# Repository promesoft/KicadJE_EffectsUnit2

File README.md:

# KicadJE_EffectsUnit2
Distortion test base

# Purpose
Use for Distortion Effects unit and Distortion pedal

# Status - Preliminary SCH/PCB Mounted
## Initial 
| Stage  | Detail | Status |
| ------------- | ------------- | ------------- |
| create material  | sch/pcb | OK  |
| | gerber | OK |
| production  |   | done |
|  | produced | done |
|  | delivered | delivered |
## Preliminary validation
| Test  | Detail | Status |
| ------------- | ------------- | ------------- |
| Initial Inspection | | OK |
| Initial Technical Test |  |  |
| Initial Product Test | EU7  | Working - but has some oscillation in some config - issues with DC coupling around the circuit and output |
| Initial Product Test | EU8  |  |

## Secondary validation
| Test  | Detail | Status |
| ------------- | ------------- |------------- |
| Product Test |  | |
| Product Test |  |  |
| Quality | | |
| Quality | | |
| Long Term Product Test |  |  |
| Power Draw |  | 

## Errata
### Errata -

## Issues and Notes
### 

# Pictures

# Other components
None

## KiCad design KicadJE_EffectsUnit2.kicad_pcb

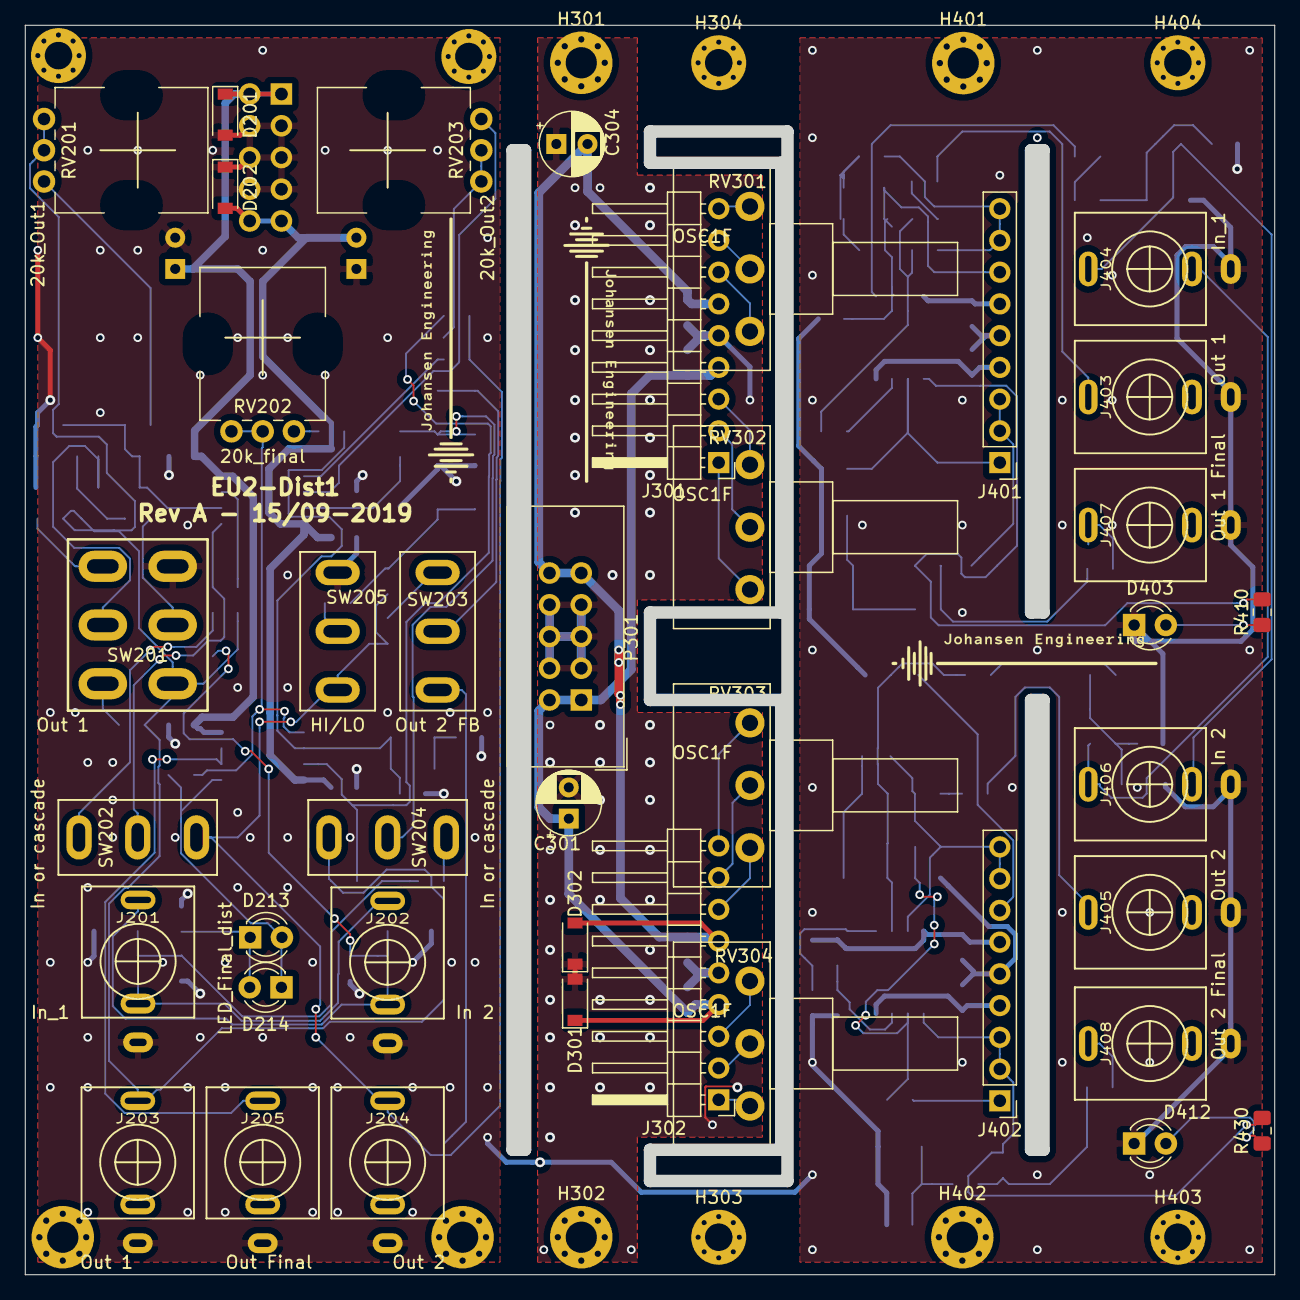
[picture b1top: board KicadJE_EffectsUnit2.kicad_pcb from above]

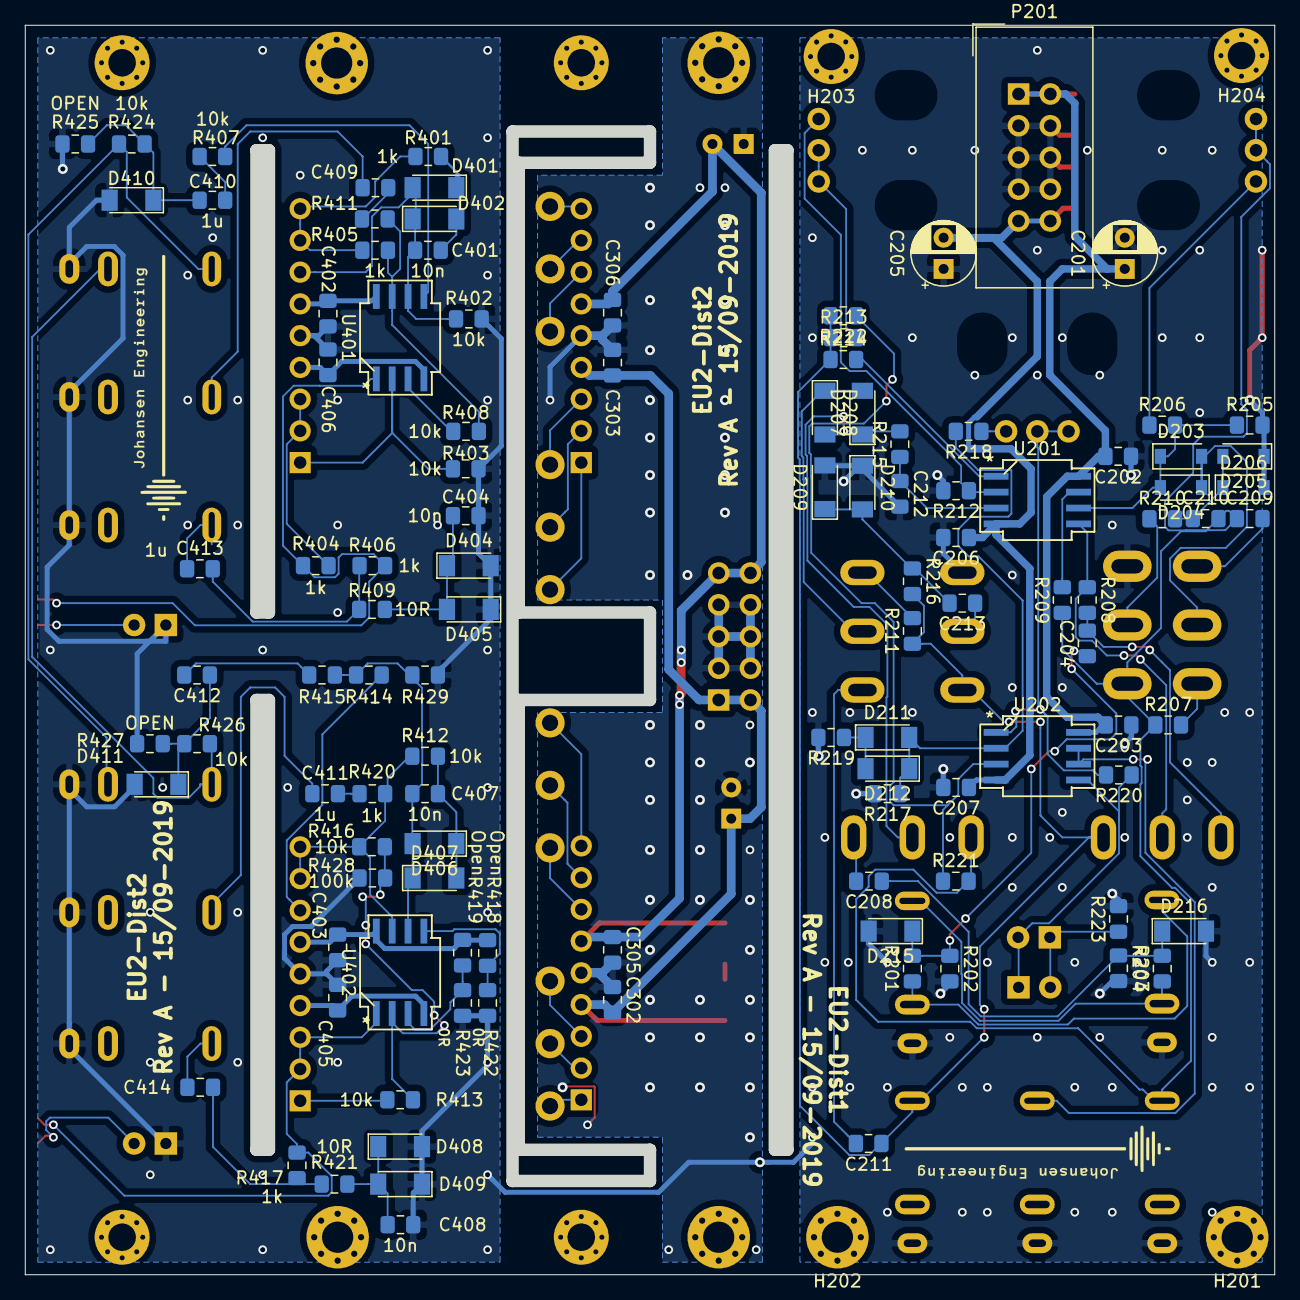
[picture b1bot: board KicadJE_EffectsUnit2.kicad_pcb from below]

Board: 2 copper layers, 100.0 x 100.0 mm, 161 parts (113 on the bottom side), 91 nets.

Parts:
C201, C205, C301, C304: 100uF 16v; CP_Radial_D5.0mm_P2.50mm
C202, C203, C206, C207, C302, C303, C305, C306, C402, C403, C405, C406: 100n; C_0805_2012Metric_Pad1.15x1.40mm_HandSolder
C204, C208, C409, C410, C411, C412, C413, C414: 1u; C_0805_2012Metric_Pad1.15x1.40mm_HandSolder
C209, C210, C211, C213: 220n; C_0805_2012Metric_Pad1.15x1.40mm_HandSolder
C212: 33n; C_0805_2012Metric_Pad1.15x1.40mm_HandSolder
C401, C404, C407, C408: 10n; C_0805_2012Metric_Pad1.15x1.40mm_HandSolder
D201, D202, D203, D204, D205, D206, D301, D302: 1N1007; D_SOD-123
D207, D208, D209, D210, D211, D212, D401, D402, D404, D405, D406, D407, D408, D409: LL4148; D_MiniMELF
D213, D214: LED_Final_dist; LED_D3.0mm
D215, D216, D410, D411: D_Zener; D_MiniMELF
D403, D412: LED; LED_D3.0mm
H201, H202, H301, H302, H401, H402: 2,5mm; MountingHole_2.5mm_Pad_Via
H203, H204, H303, H304, H403, H404: 2,2mm; MountingHole_2.2mm_M2_Pad_Via
J201, J404: In_1; PJ301SM
J202, J406: In 2; PJ301SM
J203, J403: Out 1; PJ301SM
J204, J405: Out 2; PJ301SM
J205: Out Final; PJ301SM
J301, J302: Conn_01x09_Male; PinHeader_1x09_P2.54mm_Horizontal
J401, J402: Conn_01x09_Male; PinHeader_1x09_P2.54mm_Vertical
J407: Out 1 Final; PJ301SM
J408: Out 2 Final; PJ301SM
P201, P301: Doepfer_Power_10pin; IDC-Header_2x05_Pitch2.54mm_Straight
R201, R203, R205, R207, R212, R215, R217, R221, R222, R402, R403, R407, R408, R412, R413, R415, R416, R424, R426: 10k; R_0805_2012Metric_Pad1.15x1.40mm_HandSolder
R202, R204, R425, R427: OPEN; R_0805_2012Metric_Pad1.15x1.40mm_HandSolder
R206, R213, R218: 4k7; R_0805_2012Metric_Pad1.15x1.40mm_HandSolder
R208, R428, R429: 100k; R_0805_2012Metric_Pad1.15x1.40mm_HandSolder
R209, R214: 680R; R_0805_2012Metric_Pad1.15x1.40mm_HandSolder
R210: 470R; R_0805_2012Metric_Pad1.15x1.40mm_HandSolder
R211, R220, R401, R404, R405, R406, R410, R411, R414, R417, R420, R430: 1k; R_0805_2012Metric_Pad1.15x1.40mm_HandSolder
R216, R409, R421: 10R; R_0805_2012Metric_Pad1.15x1.40mm_HandSolder
R219: 150R; R_0805_2012Metric_Pad1.15x1.40mm_HandSolder
R223: 100R; R_0805_2012Metric_Pad1.15x1.40mm_HandSolder
R418, R419: Open; R_0805_2012Metric_Pad1.15x1.40mm_HandSolder
R422, R423: 0R; R_0805_2012Metric_Pad1.15x1.40mm_HandSolder
RV201: 20k_Out1; Potentiometer_China_RK09_Single_Vertical_AJ
RV202: 20k_final; Potentiometer_China_RK09_Single_Vertical_AJ
RV203: 20k_Out2; Potentiometer_China_RK09_Single_Vertical_AJ
RV301, RV302, RV303, RV304: POT; Potentiometer_Piher_T-16H_Single_Horizontal
SW201: Out 1; SPDTx2
SW202, SW204: In or cascade; SP1MS1
SW203: Out 2 FB; SP1MS1
SW205: HI/LO; SP1MS1
U201, U202, U401, U402: TL072; AJ_SO-8_5.3x6.2mm_P1.27mm

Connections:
+12V: C402.2, C403.2, J401.6, J402.6, R418.2, R419.2, U401.8, U402.8
-12V: C405.1, C406.1, J401.4, J402.4, U401.4, U402.4
/KicadJE_EU7_Distort2/+12v: C205.2, C206.1, C207.1, D202.2, P201.9, P201.10, U201.4, U202.4
/KicadJE_EU7_Distort2/-12v: C201.1, C202.2, C203.2, D201.1, P201.1, P201.2, U201.8, U202.8
/KicadJE_EU8_Dist/POT1_C: J401.8, J401.9, R401.2, R405.1
/KicadJE_EU8_Dist/POT1_L: C401.1, D401.2, D402.1, J401.7, R402.1, U401.6
/KicadJE_EU8_Dist/POT2_C: J401.2, J401.3, R404.1
/KicadJE_EU8_Dist/POT2_L: J401.1, R403.1, U401.2
/KicadJE_EU8_Dist/POT3_C: J402.8, J402.9, R412.1, R416.2, R420.1, U402.7
/KicadJE_EU8_Dist/POT3_L: J402.7, R414.1
/KicadJE_EU8_Dist/POT4_C: J402.2, J402.3, R417.2, R430.2, U402.1
/KicadJE_EU8_Dist/POT4_L: J402.1, R413.1
/angled_panel/+12V_1: C304.2, C305.1, C306.1, D302.2, J301.6, J302.6, P301.9, P301.10
/angled_panel/-12V_1: C301.1, C302.2, C303.2, D301.1, J301.4, J302.4, P301.1, P301.2
/angled_panel/GND_1: C301.2, C302.1, C303.1, C304.1, C305.2, C306.2, D301.2, D302.1, J301.5, J302.5, P301.3, P301.4, P301.5, P301.6, P301.7, P301.8
/angled_panel/POT1_C: J301.8, RV301.2
/angled_panel/POT1_H: J301.9, RV301.3
/angled_panel/POT1_L: J301.7, RV301.1
/angled_panel/POT2_C: J301.2, RV302.2
/angled_panel/POT2_H: J301.3, RV302.3
/angled_panel/POT2_L: J301.1, RV302.1
/angled_panel/POT3_C: J302.8, RV303.2
/angled_panel/POT3_H: J302.9, RV303.3
/angled_panel/POT3_L: J302.7, RV303.1
/angled_panel/POT4_C: J302.2, RV304.2
/angled_panel/POT4_H: J302.3, RV304.3
/angled_panel/POT4_L: J302.1, RV304.1
GND: C201.2, C202.1, C203.1, C205.1, C206.2, C207.2, C212.2, C402.1, C403.1, C404.2, C405.2, C406.2, C408.2, D201.2, D202.1, D205.1, D206.2, D209.2, D210.1, D215.2, D216.2, D403.1, D404.2, D405.1, D408.2, D409.1, D410.2, D411.2, D412.1, J201.S, J202.S, J203.S, J204.S, J205.S, J401.5, J402.5, J403.S, J404.S, J405.S, J406.S, J407.S, J408.S, P201.3, P201.4, P201.5, P201.6, P201.7, P201.8, R202.2, R204.2, R205.2, R212.2, R217.2, R219.2, R223.2, R402.2, R403.2, R422.1, R423.1, R425.2, R427.2, R428.2, R429.2, SW201.6, SW205.1
In1: C204.2, R208.2, SW202.1
In2: C208.2, SW204.1
In_1: C410.2, R407.2
In_2: C412.2, R415.2
unnamed: C204.1, D215.1, R201.2, R202.1
unnamed: C208.1, D216.1, R203.2, R204.1
unnamed: C209.2, SW201.3
unnamed: C210.1, D205.2, D206.1, R210.2
unnamed: C211.2, SW203.3
unnamed: C212.1, R215.1, U201.3
unnamed: C213.1, SW205.2
unnamed: C213.2, D209.1, D210.2, R216.1
unnamed: C401.2, D401.1, D402.2, R401.1
unnamed: C404.1, D404.1, D405.2, R409.1
unnamed: C407.1, D406.2, D407.1, R414.2, R415.1, R429.1, U402.6
unnamed: C407.2, D406.1, D407.2, R412.2
unnamed: C408.1, D408.1, D409.2, R421.1
unnamed: C409.1, J403.T
unnamed: C410.1, D410.1, R424.2, R425.1
unnamed: C411.1, J405.T
unnamed: C412.1, D411.1, R426.2, R427.1
unnamed: C413.1, J407.T
unnamed: C414.1, J408.T
unnamed: D203.1, D204.2, R205.1, R206.2, U201.6
unnamed: D203.2, D204.1, SW201.2
unnamed: D207.1, D208.2, R215.2, SW204.2
unnamed: D207.2, D208.1, SW203.2
unnamed: D211.1, D212.2, R219.1
unnamed: D211.2, D212.1, R217.1, R218.2, U202.2
unnamed: D213.1, D214.2, R223.1
unnamed: D213.2, D214.1, R220.1, U202.5
unnamed: D403.2, R410.1
unnamed: D412.2, R430.1
unnamed: J201.T, J202.TN, R201.1
unnamed: J201.TN, J202.T, R203.1
unnamed: J404.T, J406.TN, R424.1
unnamed: J404.TN, J406.T, R426.1
unnamed: R206.1, RV201.1
unnamed: R207.2, SW201.1
unnamed: R208.1, SW202.2, U201.5
unnamed: R209.2, U201.7
unnamed: R210.1, SW201.5
unnamed: R211.2, SW203.1
unnamed: R212.1, RV203.1, U201.2
unnamed: R213.2, RV203.2, RV203.3
unnamed: R214.2, U201.1
unnamed: R218.1, RV202.1
unnamed: R220.2, RV202.2, RV202.3, U202.1
unnamed: R221.1, R222.1, U202.3
unnamed: R404.2, R406.2, R410.2, U401.1
unnamed: R405.2, R408.2, R411.1, U401.7
unnamed: R407.1, U401.5
unnamed: R408.1, U401.3
unnamed: R413.2, R416.1, R428.1, U402.2
unnamed: R418.1, R422.2, U402.5
unnamed: R419.1, R423.2, U402.3
Out1Dist: C209.1, C210.2, J203.T, R207.1, R209.1, R221.2, RV201.2, RV201.3, SW201.4, SW204.3
Out1_Dist: C409.2, R411.2
Out1_Final: C413.2, R406.1, R409.2
Out2Dist: C211.1, J204.T, R211.1, R213.1, R214.1, R216.2, R222.2, SW202.3, SW205.3
Out2_Dist: C411.2, R420.2
Out2_Final: C414.2, R417.1, R421.2
OutFinal: J205.T, U202.6, U202.7

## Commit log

2019-05-31 Migrated from uP DAC project
2019-05-31 schematic link
2019-06-01 Distortion 2 channels
2019-06-01 2 paths in sch
2019-06-01 New DPDT footprint
2019-06-01 decoupling placed
2019-06-01 Overall placement
2019-06-02 overall design places and routed
2019-06-02 Routed
2019-06-02 Routing of Distort2 done
2019-06-02 Prepare for angled board for potmeter mount
2019-06-02 New base schematic for angled board
2019-06-02 Pin hdr
2019-06-02 Zener added to EU-7
2019-06-02 Panel board routed
2019-06-02 3D messing around
2019-09-13 Dist 2 sch
2019-09-13 PCB dist 2 placement of face panel
2019-09-14 Name diff between borad In/Out labels
2019-09-15 layers done
2019-09-15 Labels and Text
2019-09-15 Gerber
2019-09-15 drill
2019-09-15 Bom + DRC
2019-09-15 Gerber DRC
2019-10-12 Rev B init
2019-10-12 EU8 input stage
2019-10-13 Tweak values
2020-06-07 Dist
